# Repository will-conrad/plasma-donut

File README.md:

# Plasma Donut — Pico 2 firmware

C firmware (Raspberry Pi Pico SDK) for the Plasma Donut control board (UVA ECE capstone,
Fall 2026). A Raspberry Pi Pico 2 reads board temperatures, coil supply
voltages and the A/B phase signal, and shows them on a 128x64 ST7565R LCD.
**The firmware only monitors — it never controls the HV side.**

> **Firmware is being rebuilt from scratch.** The repo is an outline with no
> code yet; the previous version is in git history (commit `903789a`). The pin
> map, brief, fixes list and `docs/` are the spec for the rebuild.

## Layout

| Path | What it is |
|---|---|
| `src/` | Firmware source (empty outline): `config/`, `drivers/`, `sensors/`, `ui/`, plus `main.c`; `CMakeLists.txt` at the root (to be written) |
| `tests/host/` | Laptop-side tests (empty) |
| `tools/` | Helper scripts, e.g. deploy to the Pico (empty) |
| `PINMAP.md` | GPIO → net → function, from the KiCad netlist |
| `CLAUDE.md` | Firmware brief: architecture, conversion math, bring-up sequence |
| `FIXES.md` | Firmware side of the known board issues |
| `docs/ISSUES.md` | Known board issues the firmware works around (`ISSUES #n` in code) |
| `docs/REWORK.md` | Optional hardware bodges (gated by flags in `src/config/config.h`) |
| `docs/design-requirements.md` | Design requirements (`DC-xx` in code) |
| `docs/RULES.md` | Claim-tag rules: `(part p.N)`, `[netlist]`, `[calc]`, `[web]`, `[assumed]` |
| `docs/parts/` | Datasheet notes + `specs.csv` for the parts the firmware talks to |

The source of truth for pins is the KiCad schematic, which lives outside this
repo (OneDrive `CAPSTONE/Microcontroller-PCB/`), along with the full datasheet
PDFs that `(part p.N)` citations point to.

## Build (once the code exists)

```bash
export PICO_SDK_PATH=~/pico/pico-sdk      # SDK 2.3.1
cmake -B build -DPICO_BOARD=pico2
cmake --build build
# hold BOOTSEL, plug in the Pico 2, copy build/<target>.uf2 to the drive
```

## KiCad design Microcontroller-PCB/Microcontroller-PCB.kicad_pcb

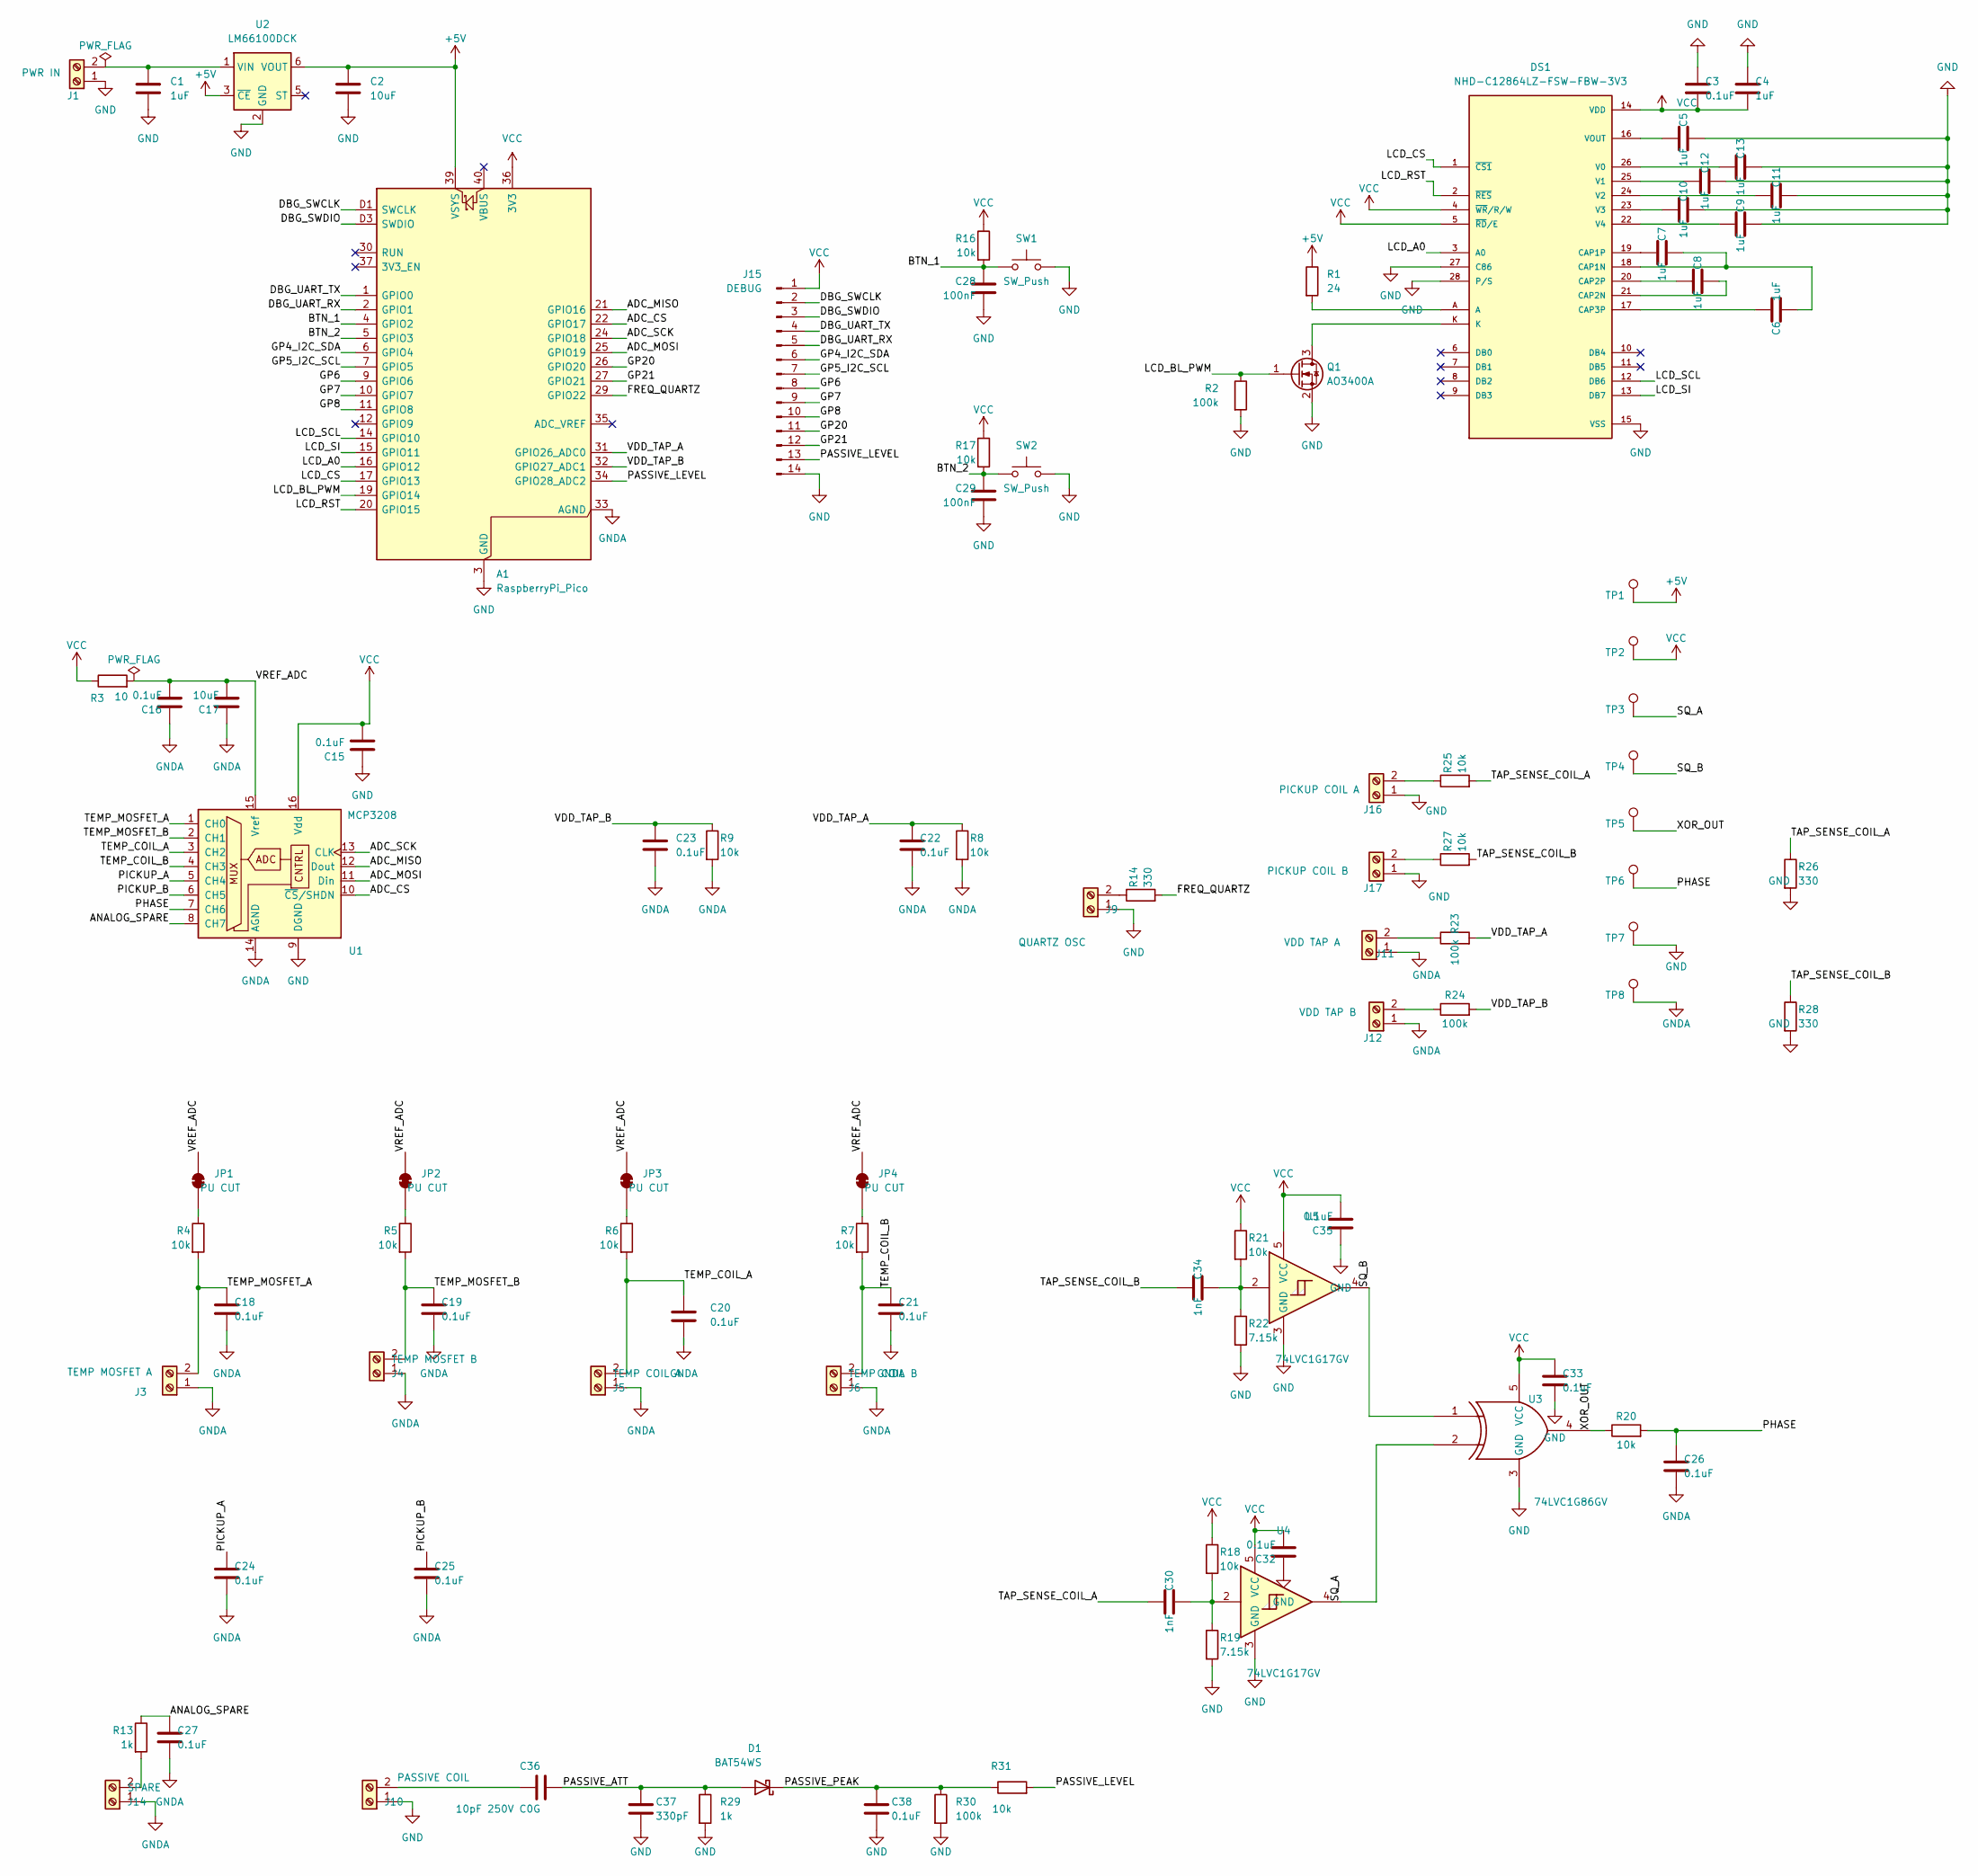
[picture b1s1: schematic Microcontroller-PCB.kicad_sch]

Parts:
A1: RaspberryPi_Pico; RaspberryPi_Pico_SMD_HandSolder
C1, C4, C5, C6, C7, C8, C9, C10, C11, C12, C13: 1uF; C_0805_2012Metric_Pad1.18x1.45mm_HandSolder
C2, C17: 10uF; C_1206_3216Metric_Pad1.33x1.80mm_HandSolder
C3, C15, C16, C18, C19, C20, C21, C22, C23, C24, C25, C26, C27, C32, C33, C35, C38: 0.1uF; C_0805_2012Metric_Pad1.18x1.45mm_HandSolder
C28, C29: 100nF; C_0805_2012Metric_Pad1.18x1.45mm_HandSolder
C30, C34: 1nF; C_0805_2012Metric_Pad1.18x1.45mm_HandSolder
C36: 10pF 250V C0G; C_0805_2012Metric_Pad1.18x1.45mm_HandSolder
C37: 330pF; C_0805_2012Metric_Pad1.18x1.45mm_HandSolder
D1: BAT54WS; D_SOD-323_HandSoldering
DS1: NHD-C12864LZ-FSW-FBW-3V3; LCD_NHD-C12864LZ-FSW-FBW-3V3; PARTREV 1.0
J1: PWR IN; TerminalBlock_Phoenix_MKDS-1,5-2_1x02_P5.00mm_Horizontal
J3: TEMP MOSFET A; TerminalBlock_Phoenix_MKDS-1,5-2_1x02_P5.00mm_Horizontal
J4: TEMP MOSFET B; TerminalBlock_Phoenix_MKDS-1,5-2_1x02_P5.00mm_Horizontal
J5: TEMP COIL A; TerminalBlock_Phoenix_MKDS-1,5-2_1x02_P5.00mm_Horizontal
J6: TEMP COIL B; TerminalBlock_Phoenix_MKDS-1,5-2_1x02_P5.00mm_Horizontal
J9: QUARTZ OSC; TerminalBlock_Phoenix_MKDS-1,5-2_1x02_P5.00mm_Horizontal
J10: PASSIVE COIL; TerminalBlock_Phoenix_MKDS-1,5-2_1x02_P5.00mm_Horizontal
J11: VDD TAP A; TerminalBlock_Phoenix_MKDS-1,5-2_1x02_P5.00mm_Horizontal
J12: VDD TAP B; TerminalBlock_Phoenix_MKDS-1,5-2_1x02_P5.00mm_Horizontal
J14: SPARE; TerminalBlock_Phoenix_MKDS-1,5-2_1x02_P5.00mm_Horizontal
J15: DEBUG; PinHeader_1x14_P2.54mm_Vertical
J16: PICKUP COIL A; TerminalBlock_Phoenix_MKDS-1,5-2_1x02_P5.00mm_Horizontal
J17: PICKUP COIL B; TerminalBlock_Phoenix_MKDS-1,5-2_1x02_P5.00mm_Horizontal
JP1, JP2, JP3, JP4: PU CUT; SolderJumper-2_P1.3mm_Bridged_RoundedPad1.0x1.5mm
Q1: AO3400A; SOT-23
R1: 24; R_1206_3216Metric_Pad1.30x1.75mm_HandSolder
R2, R23, R24, R30: 100k; R_0805_2012Metric_Pad1.20x1.40mm_HandSolder
R3: 10; R_0805_2012Metric_Pad1.20x1.40mm_HandSolder
R4, R5, R6, R7, R8, R9, R16, R17, R18, R20, R21, R25, R27, R31: 10k; R_0805_2012Metric_Pad1.20x1.40mm_HandSolder
R13, R29: 1k; R_0805_2012Metric_Pad1.20x1.40mm_HandSolder
R14, R26, R28: 330; R_0805_2012Metric_Pad1.20x1.40mm_HandSolder
R19, R22: 7.15k; R_0805_2012Metric_Pad1.20x1.40mm_HandSolder
SW1, SW2: SW_Push; SW_PUSH_6mm
TP1: +5V; TestPoint_THTPad_D2.0mm_Drill1.0mm
TP2: 3V3; TestPoint_THTPad_D2.0mm_Drill1.0mm
TP3: SQ A; TestPoint_THTPad_D2.0mm_Drill1.0mm
TP4: SQ B; TestPoint_THTPad_D2.0mm_Drill1.0mm
TP5: XOR; TestPoint_THTPad_D2.0mm_Drill1.0mm
TP6: PHASE; TestPoint_THTPad_D2.0mm_Drill1.0mm
TP7: GND; TestPoint_THTPad_D2.0mm_Drill1.0mm
TP8: GNDA; TestPoint_THTPad_D2.0mm_Drill1.0mm
U1: MCP3208; SOIC-16_3.9x9.9mm_P1.27mm
U2: LM66100DCK; SOT-363_SC-70-6
U3: 74LVC1G86GV; 74LVC1G86GV_125
U4, U5: 74LVC1G17GV; SOT95P275X110-5N

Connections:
+5V: A1.39 (VSYS), C2.1, R1.1, TP1.1, U2.3 (~CE), U2.6 (VOUT)
/ADC_CS: A1.22 (GPIO17), U1.10 (~CS/SHDN)
/ADC_MISO: A1.21 (GPIO16), U1.12 (Dout)
/ADC_MOSI: A1.25 (GPIO19), U1.11 (Din)
/ADC_SCK: A1.24 (GPIO18), U1.13 (CLK)
/ANALOG_SPARE: C27.1, R13.1, U1.8 (CH7)
/BTN_1: A1.4 (GPIO2), C28.1, R16.2, SW1.1
/BTN_2: A1.5 (GPIO3), C29.1, R17.2, SW2.1
/DBG_SWCLK: A1.D1 (SWCLK), J15.2
/DBG_SWDIO: A1.D3 (SWDIO), J15.3
/DBG_UART_RX: A1.2 (GPIO1), J15.5
/DBG_UART_TX: A1.1 (GPIO0), J15.4
/FREQ_QUARTZ: A1.29 (GPIO22), R14.2
/GP4_I2C_SDA: A1.6 (GPIO4), J15.6
/GP5_I2C_SCL: A1.7 (GPIO5), J15.7
/GP6: A1.9 (GPIO6), J15.8
/GP7: A1.10 (GPIO7), J15.9
/GP8: A1.11 (GPIO8), J15.10
/GP20: A1.26 (GPIO20), J15.11
/GP21: A1.27 (GPIO21), J15.12
/LCD_A0: A1.16 (GPIO12), DS1.3 (A0)
/LCD_BL_PWM: A1.19 (GPIO14), Q1.1 (G), R2.1
/LCD_CS: A1.17 (GPIO13), DS1.1 (~CS1)
/LCD_RST: A1.20 (GPIO15), DS1.2 (~RES)
/LCD_SCL: A1.14 (GPIO10), DS1.12 (DB6)
/LCD_SI: A1.15 (GPIO11), DS1.13 (DB7)
/PASSIVE_ATT: C36.2, C37.1, D1.2 (A), R29.1
/PASSIVE_LEVEL: A1.34 (GPIO28_ADC2), J15.13, R31.2
/PASSIVE_PEAK: C38.1, D1.1 (K), R30.1, R31.1
/PHASE: C26.1, R20.2, TP6.1, U1.7 (CH6)
/PICKUP_A: C24.1, U1.5 (CH4)
/PICKUP_B: C25.1, U1.6 (CH5)
/SQ_A: TP3.1, U3.2, U4.4
/SQ_B: TP4.1, U3.1, U5.4
/TAP_SENSE_COIL_A: C30.1, R25.2, R26.1
/TAP_SENSE_COIL_B: C34.1, R27.2, R28.1
/TEMP_COIL_A: C20.1, J5.2, R6.2, U1.3 (CH2)
/TEMP_COIL_B: C21.1, J6.2, R7.2, U1.4 (CH3)
/TEMP_MOSFET_A: C18.1, J3.2, R4.2, U1.1 (CH0)
/TEMP_MOSFET_B: C19.1, J4.2, R5.2, U1.2 (CH1)
/VDD_TAP_A: A1.31 (GPIO26_ADC0), C22.1, R8.1, R23.2
/VDD_TAP_B: A1.32 (GPIO27_ADC1), C23.1, R9.1, R24.2
/VREF_ADC: C16.2, C17.2, JP1.2 (B), JP2.2 (B), JP3.2 (B), JP4.2 (B), R3.2, U1.15 (Vref)
/XOR_OUT: R20.1, TP5.1, U3.4
GND: A1.3 (GND), A1.8 (GND), A1.13 (GND), A1.18 (GND), A1.23 (GND), A1.28 (GND), A1.38 (GND), A1.D2 (GND), C1.2, C2.2, C3.1, C4.1, C5.2, C9.2, C10.2, C11.2, C12.2, C13.2, C15.1, C28.2, C29.2, C32.1, C33.2, C35.1, C37.2, C38.2, DS1.15 (VSS), DS1.27 (C86), DS1.28 (P/S), J1.1, J9.1, J10.1, J15.14, J16.1, J17.1, Q1.2 (S), R2.2, R19.2, R22.2, R26.2, R28.2, R29.2, R30.2, SW1.2, SW2.2, TP7.1, U1.9 (DGND), U2.2 (GND), U3.3 (GND), U4.3 (GND), U5.3 (GND)
GNDA: A1.33 (AGND), C16.1, C17.1, C18.2, C19.2, C20.2, C21.2, C22.2, C23.2, C24.2, C25.2, C26.2, C27.2, J3.1, J4.1, J5.1, J6.1, J11.1, J12.1, J14.1, R8.2, R9.2, TP8.1, U1.14 (AGND)
unnamed: C30.2, R18.2, R19.1, U4.2
unnamed: C34.2, R21.2, R22.1, U5.2
unnamed: C6.1, C7.2, DS1.18 (CAP1N)
unnamed: C7.1, DS1.19 (CAP1P)
unnamed: C8.2, DS1.21 (CAP2N)
unnamed: C8.1, DS1.20 (CAP2P)
unnamed: C6.2, DS1.17 (CAP3P)
unnamed: DS1.A, R1.2
unnamed: C13.1, DS1.26 (V0)
unnamed: C12.1, DS1.25 (V1)
unnamed: C11.1, DS1.24 (V2)
unnamed: C10.1, DS1.23 (V3)
unnamed: C9.1, DS1.22 (V4)
unnamed: C5.1, DS1.16 (VOUT)
unnamed: C1.1, J1.2, U2.1 (VIN)
unnamed: J9.2, R14.1
unnamed: C36.1, J10.2
unnamed: J11.2, R23.1
unnamed: J12.2, R24.1
unnamed: J14.2, R13.2
unnamed: J16.2, R25.1
unnamed: J17.2, R27.1
unnamed: JP1.1 (A), R4.1
unnamed: JP2.1 (A), R5.1
unnamed: JP3.1 (A), R6.1
unnamed: JP4.1 (A), R7.1
unnamed: DS1.K, Q1.3 (D)
VCC: A1.36 (3V3), C3.2, C4.2, C15.2, C32.2, C33.1, C35.2, DS1.4 (~WR/R/W), DS1.5 (~RD/E), DS1.14 (VDD), J15.1, R3.1, R16.1, R17.1, R18.1, R21.1, TP2.1, U1.16 (Vdd), U3.5 (VCC), U4.5 (VCC), U5.5 (VCC)

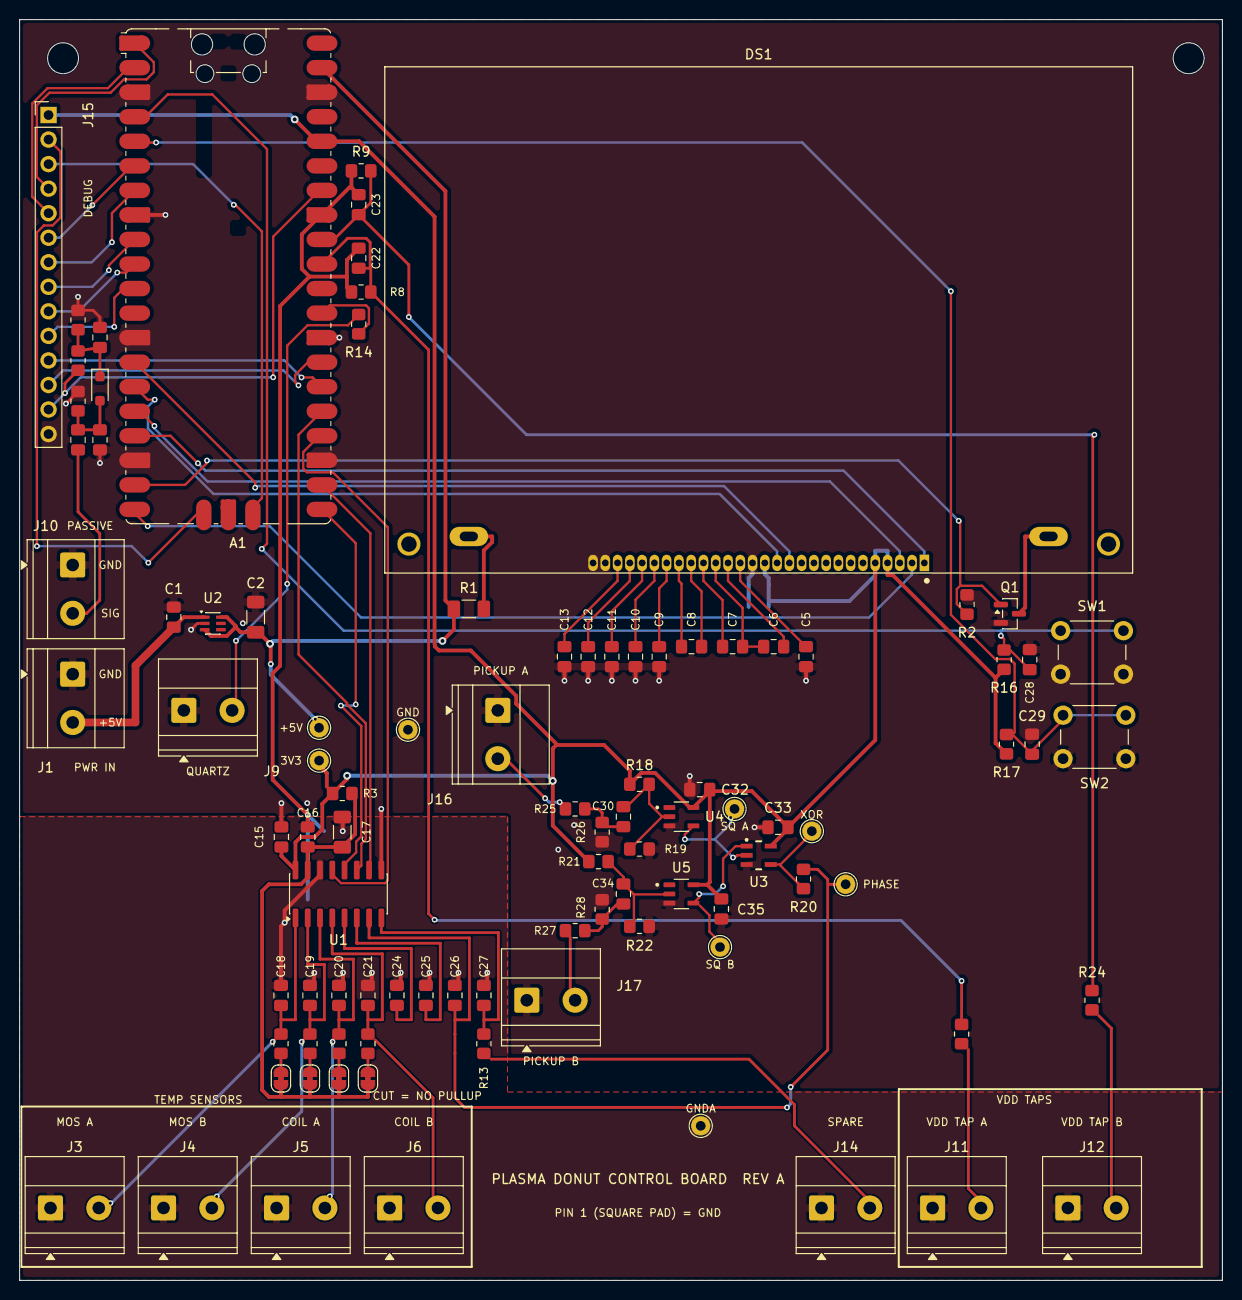
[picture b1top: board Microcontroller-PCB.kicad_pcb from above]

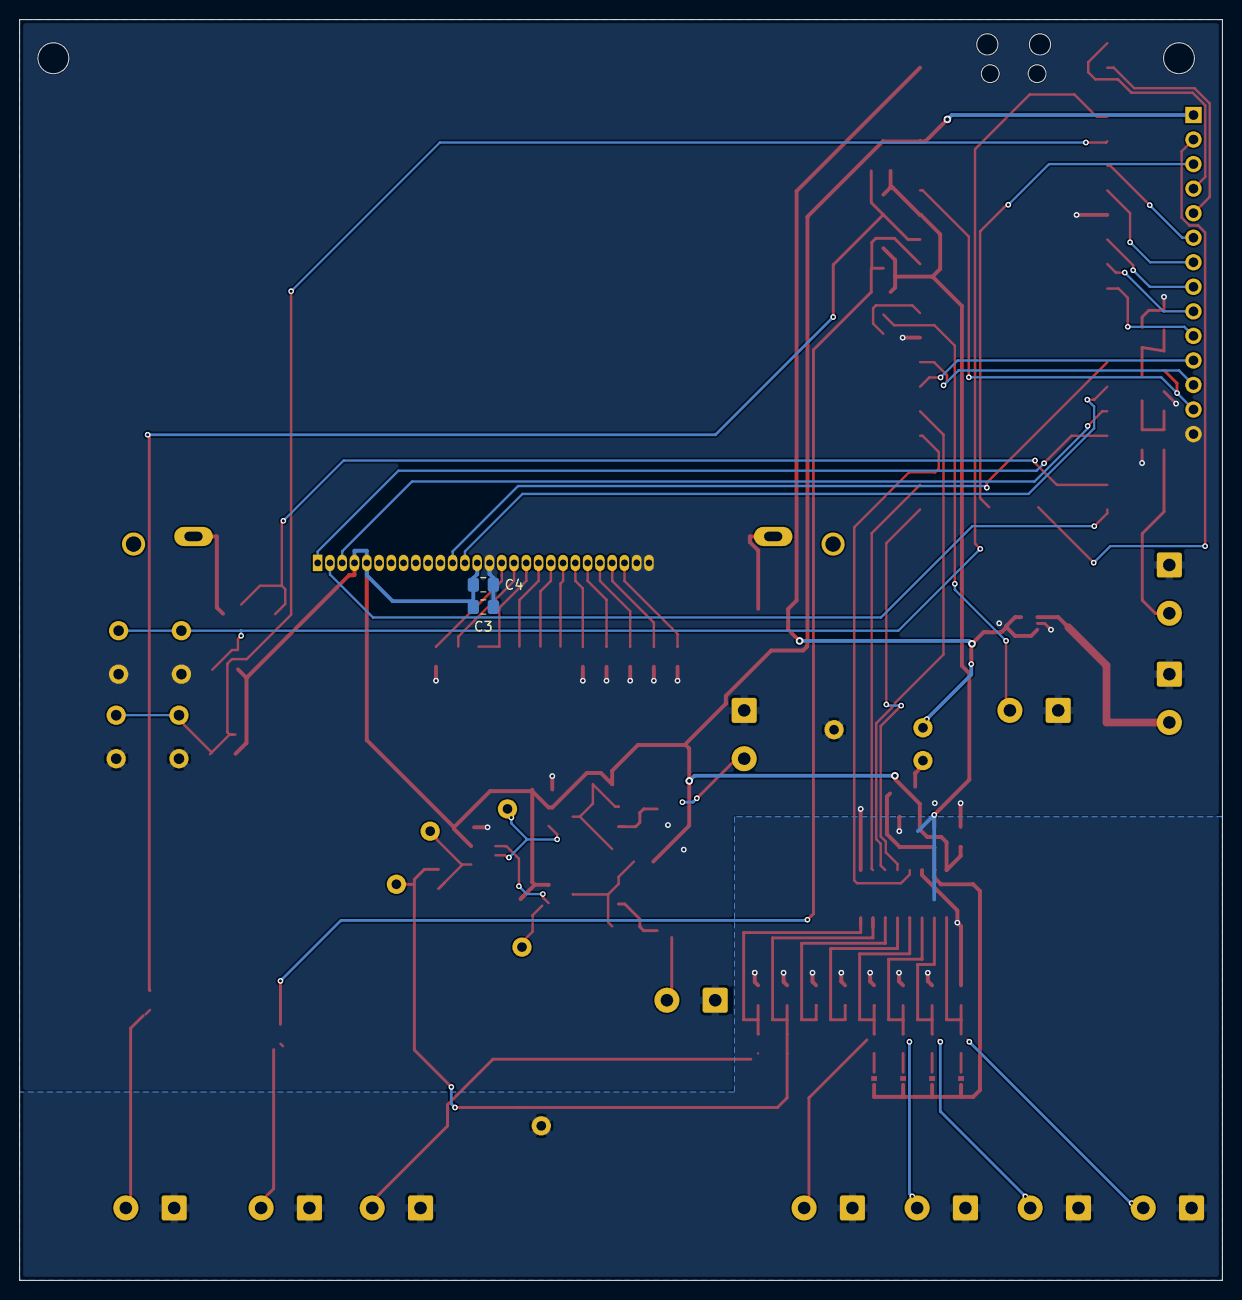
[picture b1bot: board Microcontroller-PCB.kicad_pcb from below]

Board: 2 copper layers, 124.5 x 130.5 mm, 101 parts (2 on the bottom side), 74 nets.

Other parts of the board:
H1, H2: M3; MountingHole_3.2mm_M3

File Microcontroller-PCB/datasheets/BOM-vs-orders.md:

# BOM vs parts orders

**Inputs:**
- BOM: `kicad-cli sch export bom` on `Microcontroller-PCB.kicad_sch` (2026-10-22)
- Order sheets in `CAPSTONE/Parts Orders/`:
  - **O4** = `PlasmaDonut-PartsOrder3.xlsx` (submitted for the Sep 29 order 4; Digi-Key week-04 parts arrived around Oct 8)
  - **ADD** = `PlasmaDonut-PartsOrder-Additions.xlsx` (Sep 29). It has **no stock or price columns filled**, so it's unclear whether it was ever submitted.
  - **O8** = `Plasma Bagel-PartsOrder8.xlsx` (Oct 27–28). Course email on 10/30: "The Digikey order from last week is very delayed".
- Course email 10/28 (Prof. Crockett): BAT54WS-7-F was back-ordered, so O8 lists the MCC **BAT54WS-TP** instead.

**Status key:** ✅ ordered and should be in hand · 🚚 on order 8 (in transit, delayed) · ❓ only on the Additions sheet, check the bin · — no part needed

| Ref | Qty | Value / function | Ordered MPN | Sheet | Ordered qty | Status | Notes |
|---|---|---|---|---|---|---|---|
| A1 | 1 | Raspberry Pi Pico 2 | SC1631 | O4 | 2 | ✅ | 1 spare |
| U1 | 1 | MCP3208 SOIC-16 | MCP3208-CI/SL | O4 | 2 | ✅ | + 1× MCP3208-CI/P (DIP) spare; C grade (INL ±2 LSB) |
| U2 | 1 | LM66100 | LM66100DCKR | O4 | 2 | ✅ | |
| U3 | 1 | XOR | 74LVC1G86GV,125 (Nexperia) | O4 | 3 | ✅ | 2 spare |
| U4, U5 | 2 | Schmitt buffer | 74LVC1G17GV-Q100,1 (Nexperia) | O4 | 3 | ✅ | 1 spare |
| Q1 | 1 | AO3400A | AO3400A | O4 | 2 | ✅ | |
| DS1 | 1 | LCD | NHD-C12864LZ-FSW-FBW-3V3 | O4 | 1 | ✅ | **no spare** |
| D1 | 1 | Schottky | BAT54WS-TP (MCC) | O8 | 10 | 🚚 | -7-F back-ordered; 9 spare once here |
| C1, C4–C13 | 11 | 1 µF X7R 25 V 0805 | C0805C105K3RACTU | O4 | 50 | ✅ | |
| C2, C17 | 2 | 10 µF X7R 35 V 1206 | CL31B106KLHNNNE | O4 | 10 | ✅ | |
| C3, C15, C16, C18–C27, C32, C33, C35, C38, C28, C29 | 19 | 0.1 µF X7R 0805 | CL21B104KBCNNNC | O4 | 50 | ✅ | + 10× C0805C104J5RACTU (Brennan, O8) |
| C30, C34 | 2 | 1 nF C0G 0805 | C0805C102J5GACTU | ADD | 10 | ❓ | Fallbacks: C323C102KAG5TA 1 nF radial (O8), GRM1885C1H103JA01D 10 nF 0603 (O8) |
| C36 | 1 | 10 pF C0G (≥250 V) | C0805C100JCGACTU (500 V) | O8 | 5 | 🚚 | |
| C37 | 1 | 330 pF C0G | C0805C331G5GACTU | O8 | 5 | 🚚 | |
| R1 | 1 | 24 Ω 1206 | RC1206FR-0724RL | O4 | 10 | ✅ | |
| R2, R23, R24, R30 | 4 | 100k | RC0805FR-07100KL | O4 | 25 | ✅ | 82k (RC0805FR-0782KL, ADD) not needed: the schematic now uses 100k (÷11) |
| R3 | 1 | 10 Ω | RC0805FR-0710RL | ADD | 10 | ❓ | Fallback: solder bridge (DC-04) |
| R4–R9, R16–R18, R20, R21, R25, R27, R31 | 14 | 10k | RC0805FR-0710KL | O4 | 50 | ✅ | + 10× SG73P1JTTD1002F (O8) |
| R13, R29 | 2 | 1k | RC0805FR-071KL | O4 | 15 | ✅ | 13 spare (useful for ISSUES #4/#6) |
| R14, R26, R28 | 3 | 330 Ω | RC0805FR-07330RL | O4 | 25 | ✅ | |
| R19, R22 | 2 | 7.15k | RC0805FR-077K15L | O8 | 10 | 🚚 | Fallback: 10k (bias 1.65 V) |
| J1, J3–J6, J9–J12, J14, J16, J17 | 12 | 2-pos 5.0 mm screw terminal | 1715022 (Phoenix MKDS 1,5/2) | O8 | 14 | 🚚 | Footprint is MKDS-1,5-2 P5.00 ✅. The JST XH parts on ADD **don't fit** this footprint |
| J15 | 1 | 1×14 2.54 mm header | PRPC014SAAN-RC | ADD | 2 | ❓ | Any 0.1" header strip works |
| SW1, SW2 | 2 | 6 mm tactile | B3F-1000 | ADD | 4 | ❓ | |
| TP1–TP8 | 8 | THT test pads (Ø1.0 mm drill) | (Keystone 4952 hooks on O8, Brennan) | O8 | 10 | 🚚/— | Pads also work bare or with a wire loop |
| JP1–JP4 | 4 | solder jumpers | — | — | — | — | copper only |
| (holes) | 2 | M3 mounting holes | hardware | — | — | — | |
| (off-board) | 4 | NTC 10k | NTCS0603E3103FLT | O4 | 10 | ✅ | 6 spare |
| (tool) | 1 | Pi Debug Probe | SC0889 | O4 | 1 | ✅ | for J15 SWD |

## Ordered but not on the control board
- **HV boards (Brennan / Alexis):** IPB17N25S3100ATMA1, UCC27614DR, LFSPXO025876 (13.56 MHz **5 V** HCMOS oscillator, which drives J9, see ISSUES #6), Si5351 board, LM2576S-12, MBR360, IRF530N, NE555, HV caps, AJ20-4 trimmer, and others
- **O4:** 105-0752/0753 barrel jacks (the board uses a screw terminal for J1), ZS1052/ATB322524 (spark board)
- **ADD:** JST XH headers, housings and crimps (superseded by the screw terminals), and 82k resistors (superseded by 100k)

## What this means right now
- If order 8 is still in transit, you can't populate the screw terminals, the 7.15k resistors or the passive-coil detector. Every one has a stop-gap in ISSUES #1.
- Before soldering, check the parts bin for the four ❓ lines (1 nF C0G, 10 Ω, B3F switches, header).

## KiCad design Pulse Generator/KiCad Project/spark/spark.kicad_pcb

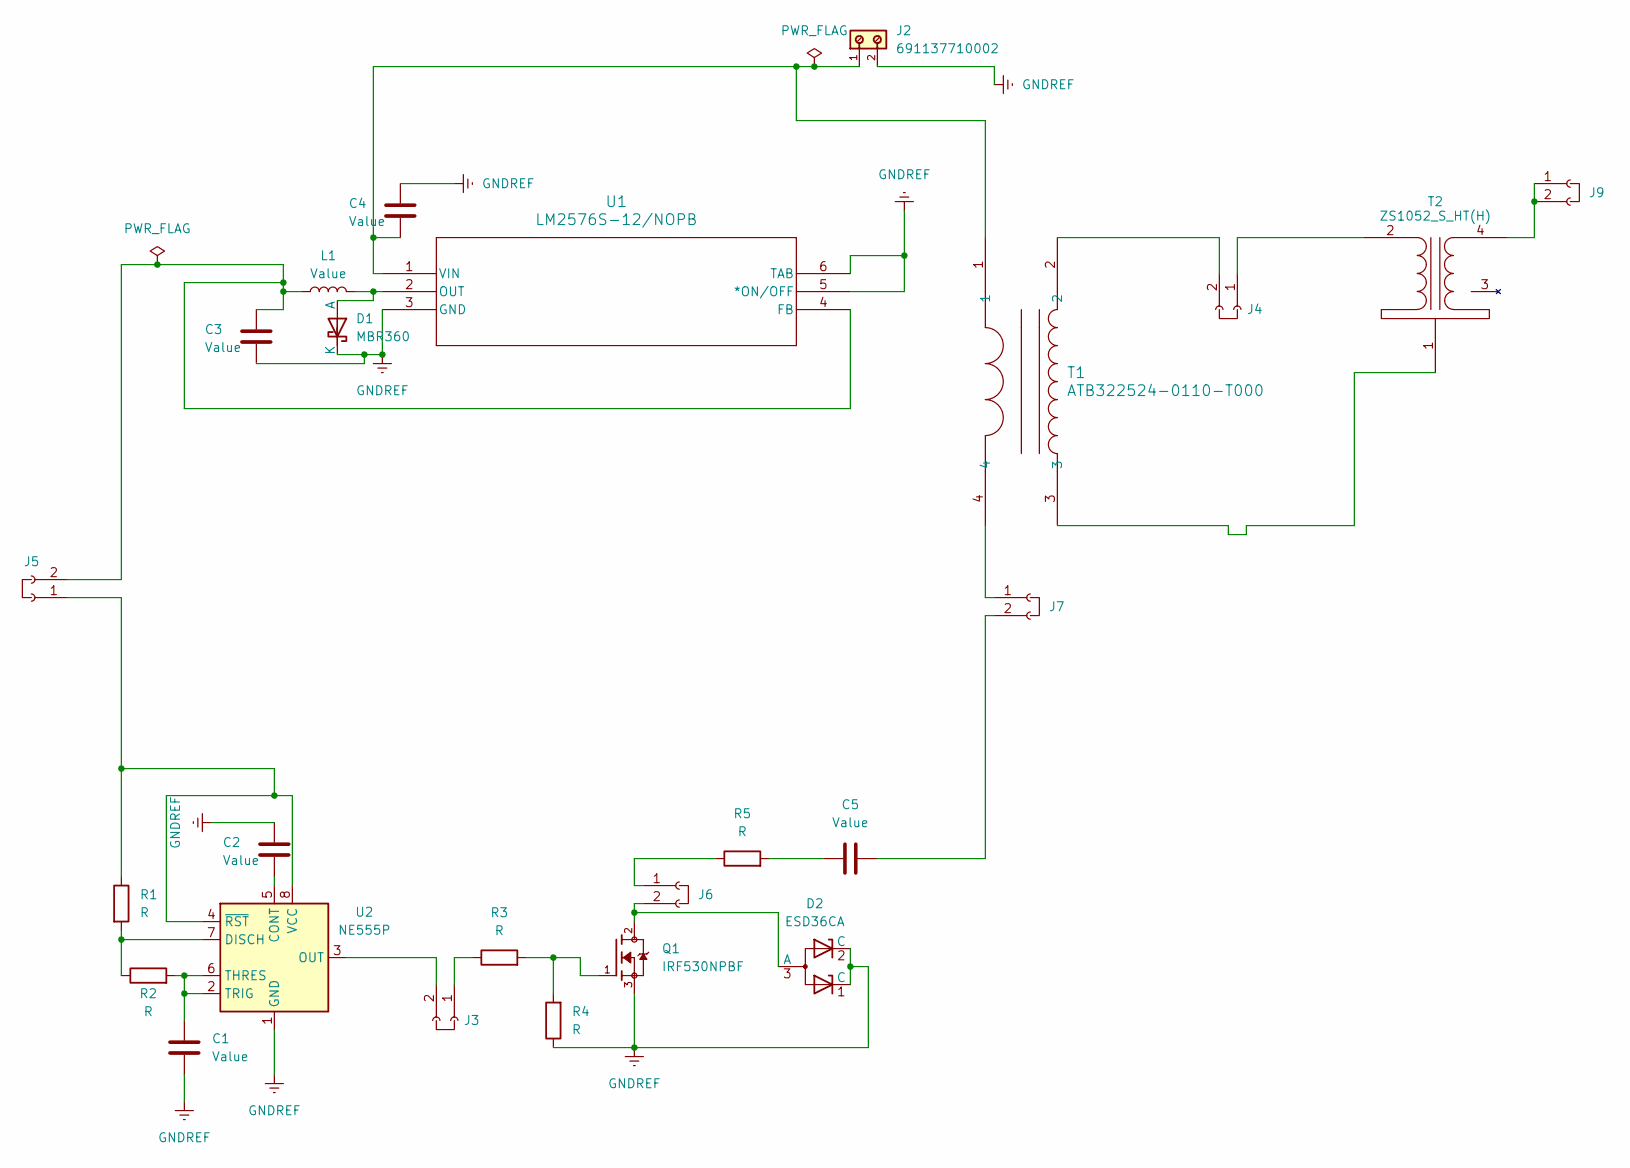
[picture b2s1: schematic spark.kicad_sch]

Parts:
C1, C2, C3, C4, C5: Value; capacitor_200mil_pitch
D1: MBR360; P2_DO-201
D2: ESD36CA; P200_SOT-23
J2: 691137710002
J3, J4, J5, J6, J7, J9: 0; 2_pin_header
L1: Value; inductor
Q1: IRF530NPBF; TO254P1041X444X1930-3; PARTREV 01/30/04; DigiKey_Part_Number IRF530NPBF-ND
R1, R2, R3, R4, R5: R; resistor_horizontal
T1: ATB322524-0110-T000; CHOKE_524-0110-T000_TDK
T2: ZS1052_S_HT(H); ZS1052 S HT(H)
U1: LM2576S-12/NOPB; TS5B_TEX
U2: NE555P; DIP-8_W7.62mm

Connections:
GNDREF: C1.2, C2.2, C3.1, C4.2, D1.2 (K), D2.1 (C), D2.2 (C), J2.2, Q1.3, R4.1, U1.3 (GND), U1.5 (*ON/OFF), U1.6 (TAB), U2.1 (GND)
unnamed: C5.1, R5.2
unnamed: D1.1 (A), L1.2, U1.2 (OUT)
unnamed: D2.3 (A), J6.2, Q1.2
unnamed: J3.1, R3.1
unnamed: J3.2, U2.3 (OUT)
unnamed: J4.1, T2.2 (AA)
unnamed: J4.2, T1.2
unnamed: J5.1, R1.1, U2.4 (~RST), U2.8 (VCC)
unnamed: C3.2, J5.2, L1.1, U1.4 (FB)
unnamed: J6.1, R5.1
unnamed: J7.1, T1.4
unnamed: C5.2, J7.2
unnamed: J9.1, J9.2, T2.4 (SB)
unnamed: Q1.1, R3.2, R4.2
unnamed: T1.3, T2.1 (AB)
unnamed: C4.1, J2.1, T1.1, U1.1 (VIN)
unnamed: C2.1, U2.5 (CONT)
unnamed: R1.2, R2.1, U2.7 (DISCH)
unnamed: C1.1, R2.2, U2.2 (TRIG), U2.6 (THRES)

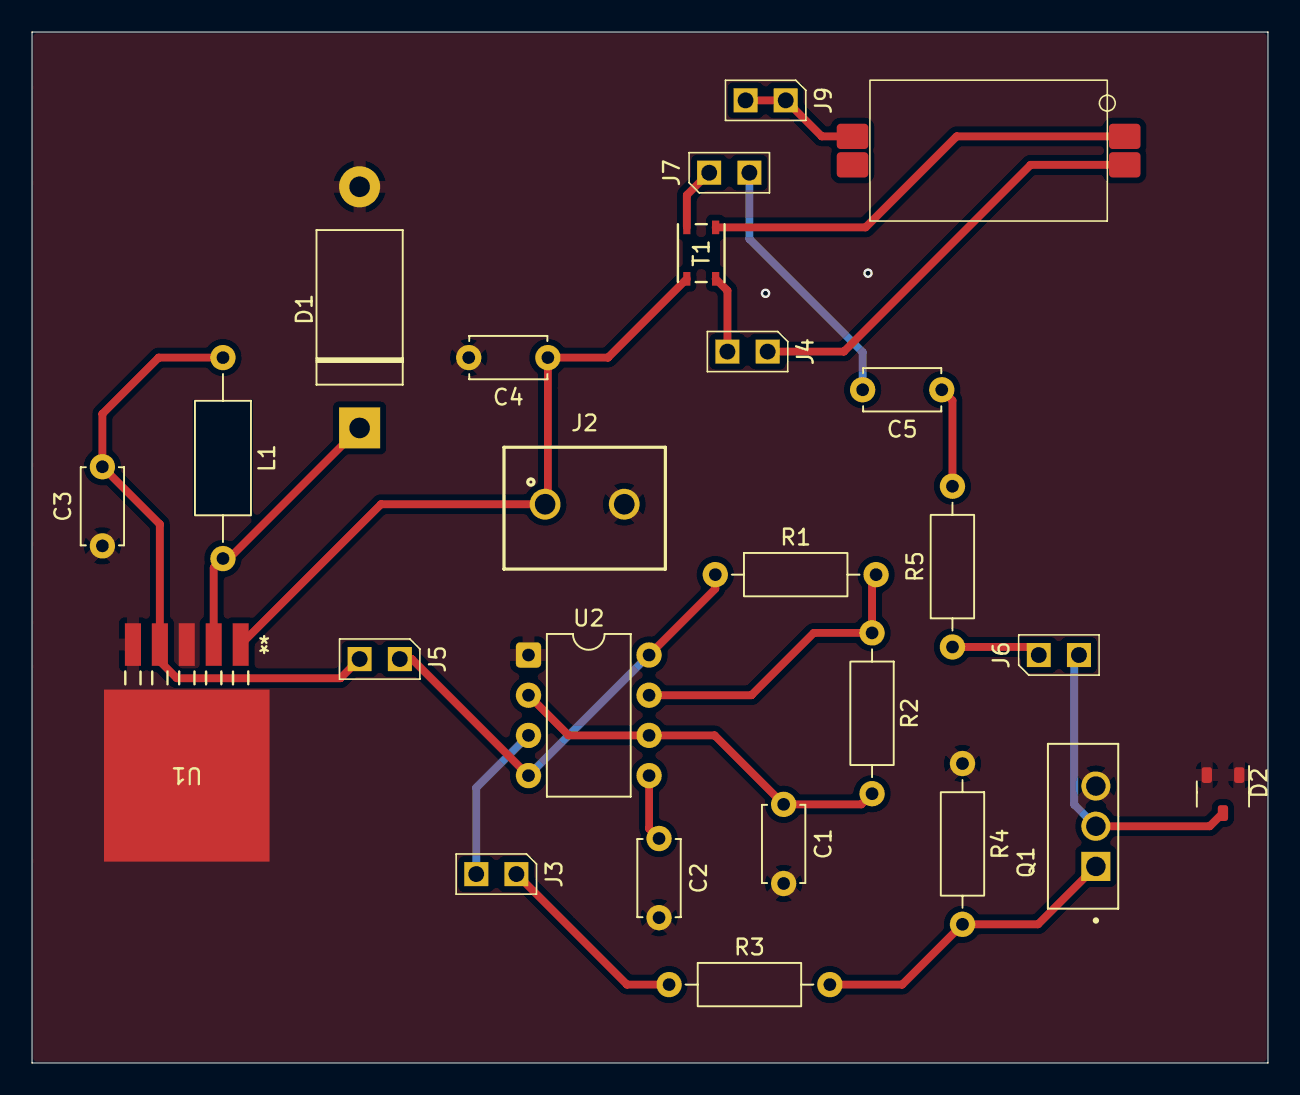
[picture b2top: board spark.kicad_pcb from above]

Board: 2 copper layers, 78.1 x 65.2 mm, 25 parts (0 on the bottom side), 20 nets.

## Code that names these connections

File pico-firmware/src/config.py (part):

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
# ---------------------------------------------------------------- GPIO map
# Buttons (active low; external 10k pull-ups R16/R17 to VCC, 100 nF to GND)
PIN_BTN_1 = 2          # /BTN_1   -> SW1
PIN_BTN_2 = 3          # /BTN_2   -> SW2

# LCD, ST7565R, 4-wire SPI on SPI1 (write-only, no MISO)
LCD_SPI_ID = 1
PIN_LCD_SCL = 10       # /LCD_SCL -> DS1 pin 12 (DB6 = SCL in serial mode), SPI1 SCK
PIN_LCD_SI = 11        # /LCD_SI  -> DS1 pin 13 (DB7 = SI),                SPI1 TX
PIN_LCD_A0 = 12        # /LCD_A0  -> DS1 pin 3  (data / command)
PIN_LCD_CS = 13        # /LCD_CS  -> DS1 pin 1  (/CS1), driven as plain GPIO
PIN_LCD_BL = 14        # /LCD_BL_PWM -> Q1 gate (AO3400A), PWM7 channel A
PIN_LCD_RST = 15       # /LCD_RST -> DS1 pin 2  (/RES)

# MCP3208 on SPI0 (separate bus from the LCD)
ADC_SPI_ID = 0
PIN_ADC_MISO = 16      # /ADC_MISO -> U1 Dout
PIN_ADC_CS = 17        # /ADC_CS   -> U1 /CS, driven as plain GPIO
PIN_ADC_SCK = 18       # /ADC_SCK  -> U1 CLK
PIN_ADC_MOSI = 19      # /ADC_MOSI -> U1 Din

# Frequency input. GPIO22 is EVEN => PWM channel A => no hardware edge
# counting. Needs a PIO edge counter.
PIN_FREQ_OSC = 22      # /FREQ_QUARTZ <- R14 (330 R) <- J9 "QUARTZ OSC"

# Pico internal ADC (RP2350, 12-bit, reference = ADC_VREF pin, not VREF_ADC)
PIN_VDD_TAP_A = 26     # ADC0  /VDD_TAP_A      (J11 via 100k / 10k divider)
PIN_VDD_TAP_B = 27     # ADC1  /VDD_TAP_B      (J12 via 100k / 10k divider)
PIN_PASSIVE_LEVEL = 28 # ADC2  /PASSIVE_LEVEL  (peak-detected passive coil, also on J15.13)
ADC_CH_VDD_A = 0
ADC_CH_VDD_B = 1
ADC_CH_PASSIVE = 2

# Debug header J15 (no HV connection). Leave as high-impedance inputs.
PIN_DBG_UART_TX = 0    # J15.4
PIN_DBG_UART_RX = 1    # J15.5
PINS_J15_SPARE = (4, 5, 6, 7, 8, 20, 21)   # J15.6..J15.12; 4/5 labelled I2C SDA/SCL
# GPIO9 is unconnected.

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MCP_CH_TEMP_MOS_B = 1
MCP_CH_TEMP_COIL_A = 2
MCP_CH_TEMP_COIL_B = 3
MCP_CH_PICKUP_A = 4    # NOT DRIVEN: net /PICKUP_A has only C24 on it
MCP_CH_PICKUP_B = 5    # NOT DRIVEN: net /PICKUP_B has only C25 on it
MCP_CH_PHASE = 6       # XOR output after R20 / C26
MCP_CH_SPARE = 7       # J14 "SPARE" via R13 (1k) / C27
MCP_SPI_BAUD = 1_000_000   # max 1.0 MHz at 2.7 V / 2.0 MHz at 5 V (mcp3208 p.3); 3.3 V not specified -> stay at 1 MHz
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
# ISSUES #5 -- optional bodge: TP3 (SQ_A) -> J15.7 (GP5), TP4 (SQ_B) -> J15.9 (GP7), each via 330 R.
BODGE_SQ_TO_GP5_GP7 = False         # set True only after REWORK.md step R5a
PIN_SQ_A = 5
PIN_SQ_B = 7

# ISSUES #6 -- GPIO22 is an even pin (no PWM edge count). It is GPIN1 (RP2350 DS p.19), so the
# on-chip frequency counter FC0 can measure it. "fc0" = FC0 on GPIN1, "pio" = PIO edge counter.
FREQ_METHOD = "fc0"
FC0_INTERVAL = 15                   # 2**15 us ~ 32 ms -> +/-62.5 Hz (RP2350 DS Table 574, p.476)
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
# ISSUES #16 -- unused GPIOs: enable pull-ups so they never float in the RP2350-E9 region.
PINS_UNUSED_PULLUP = tuple(p for p in (4, 5, 6, 7, 8, 9, 20, 21)
                           if not (BODGE_SQ_TO_GP5_GP7 and p in (PIN_SQ_A, PIN_SQ_B)))


# ================================================================ Datasheet-derived limits (2026-11-02)
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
